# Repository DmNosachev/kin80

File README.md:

# Kin80
Kin80 is a set of replacement PCBs and switch mounting plates for [Kinesis Contoured keyboards](https://deskthority.net/wiki/Kinesis_Contoured).

It is not a drop-in replacement controllers like Stapelberg or KinT (for these controllers I developed a cheap alternative called [kinBP](https://github.com/DmNosachev/kinbp) (will be published soon)). Kin80 uses different matrix (12×7) and it is aimed at serious modding of the Kinesis keyboard.

## Features
- Controller with [QMK firmware](https://qmk.fm/) support.

Uses inexpensive [WeAct Studio STM32F401/STM32F411](https://github.com/WeActTC/MiniSTM32F4x1) MCU board.

The PCB has dimensions less than 100×100 mm. Many manufacturers provide additional discounts for smaller boards.

Additional pads for connecting up to 4 swithes (i.e. additional switches on the keyboard or foot pedals) and 5 free MCU pins.

- Eliminating one of the main drawbacks of Kinesis keyboards (prior to Advantage 2): rubber top row is replaced by with mechanical switches, MX or Kailh Choc.

- Replacement thumb cluster PCBs. Reversible design, additional mounting holes for compatibility with Model 110.

- Thumb cluster switch mounting plates.

## Disadvantages / shortcomings
1. It's obviously more labour intensive than drop-in controller replacement. You have to desolder the key-wells and than carry out hand-wiring of new (or stock) switches. I started designing a PCB for key-wells, but came to the conclusion that flexible boards of this size are too expensive to manufacture.

2. It's necessary to carefully cut out two windows in the keyboard case with Dremel, then glue the mounting plates there. The result will most likely not look very professional. This problem can be solved by 3D printing curved plastic plates, but I don't have the skills to design them.

3. Thumb cluster PCBs require SMD diodes (SOD-323). Soldering them by hand can be tricky for unexperienced people. I'm going to add support for through-hole diodes in the next release.

4. Top row PCB have not been tested yet.

5. Other TODO's: design universal MX/Choc top row PCB, design FR4 mounting plate for the thumb cluster.

## BOM

1. **Controller PCB** (/controller-pcb).
  - [WeAct Studio STM32F401 or STM32F411](https://github.com/WeActTC/MiniSTM32F4x1) board. You can buy them for about 6 USD at the [official Aliexpress store](https://weactstudio.aliexpress.com/). Beware of pirated copies!
  - 2 pcs: 20 cm cable with 11-pin female Micro JST connectors with 1.25 mm pitch ([Aliexpress](https://aliexpress.com/item/4000588750065.html?sku_id=10000003451067244&spm=a2g0o.store_pc_allProduct.8148356.2.6c274451oTiXZp)) for key-wells
  - 2 pcs: 10 cm cable with 7-pin female Micro JST connectors for connecting thumb clusters
  - 2 pcs: cable with 7-pin female Micro JST connectors for connecting top row clusters, 10 cm if using PCBs or 20 cm if using hand-wiring.
  - 2 pcs male Micro JST 11-pin angled or straight connectors
  - 4 pcs male Micro JST 7-pin angled or straight connectors
  - 4 pcs 3-mm LEDs
  - 4 pcs 0805 or through-hole resistors. Their value depends on the type of LEDs (I use 1.5k Ohm for orange LEDs).
  - Pair of USB Type C male and female connectors 
2. **Thumb cluster** (/thumb-pcb)
  - The design is reversible. So, a minimal batch of 5 PCBs will give you 2 pairs + 1 spare.
  - 12 pcs SOD-323 1N4148 diodes.
  - Optional: mounting plates (see /plates/thumb).
  - 2 pcs male Micro JST 7-pin angled connectors
3. **Top row cluster** (/top-pcb)
  - The PCBs are not tested yet. They also have reversible design.
  - 12 pcs SOD-323 1N4148 diodes.
  - PCBs are optional, you can use just plates (/plates/top) and make a hand-wiring with through-hole diodes.
4. **Key-wells**
  - 56 pcs 1N4148 diodes
  - Wire
5. ** Switches **
  - 80 pcs Cherry MX compatible switches or 68 pcs MX + 12 pcs Kailh Choc
  - Optional: switch opener (if you reuse the stock switches)
  
## Buid guide
1. Disassemble the keyboard. Remove all screws and remove all PCBs. Сut the melted pins on the back plates of the top clusters.
2. Desolder the key-well PCBs. If you do not plan to use these PCBs to repair other keyboards, then you can not worry about damaging them.
3. If you plan to reuse the stock switches, then remove the diodes from them (IMHO, it will make further hand-wiring easier). Desolder the switches from thumb cluster PCBs.

You may notice that swiches are glued with hot-melt adhesive. To remove it, just wipe it with isopropyl alcohol. It will not dissolve the glue, but make it lose its adhesive properties.

4. Hand-wire the key-wells. You need *ROW2COL* direction, i.e. the anode of each diode must be connected to a switch pin, cathode (marked by black strip) — to row. See [Modern handwiring guide](https://geekhack.org/index.php?topic=87689.0).

5. Assemble thumb cluster PCBs.
6. Assemble top row PCBs or use hand-wiring.
7. Assemble the controller PCB.

8. Case. Cut two windows for new top row keys. You can use hot-melt adhesive to glue the plates to the case. Seal the holes on the back of the case with pieces of plastic. Glue the USB connector to the back of the case. Optional: use bitumen sound deadening pads to improve acoustics.

9. [Setup the QMK](https://docs.qmk.fm/).
10. Flash the firmware: `qmk flash -kb kin80 -km default`. Hold 'boot0' button on MCU board, press 'reset', then release 'boot0'.

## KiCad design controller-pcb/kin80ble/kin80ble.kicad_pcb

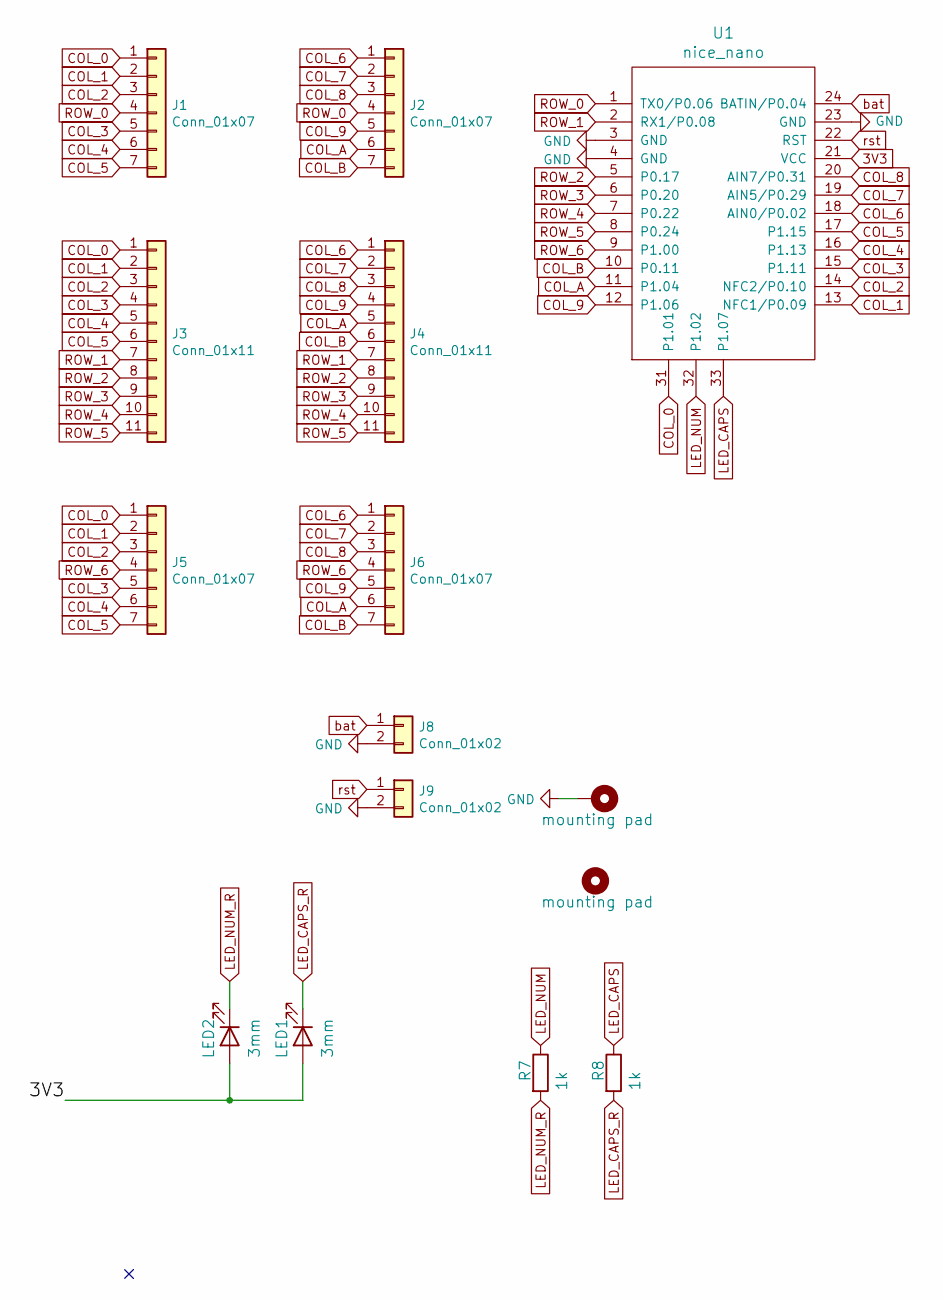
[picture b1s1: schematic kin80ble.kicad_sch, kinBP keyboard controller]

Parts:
H1: mounting pad; MountingHole_4.3mm_M4_Pad
H2: mounting pad; MountingHole_6mm
J1, J2, J5, J6: Conn_01x07; Molex_PicoBlade_53047-0710_1x07_P1.25mm_Vertical
J3, J4: Conn_01x11; Molex_PicoBlade_53047-1110_1x11_P1.25mm_Vertical
J8, J9: Conn_01x02; PinHeader_1x02_P2.54mm_Vertical
LED1, LED2: 3mm; LED_D3.0mm
R7, R8: 1k; R_Axial_DIN0207_L6.3mm_D2.5mm_P7.62mm_Horizontal
U1: nice_nano

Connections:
3V3: LED1.2 (A), LED2.2 (A), U1.21 (VCC)
COL_0: J1.1, J3.1, J5.1, U1.31 (P1.01)
COL_1: J1.2, J3.2, J5.2, U1.13 (NFC1/P0.09)
COL_2: J1.3, J3.3, J5.3, U1.14 (NFC2/P0.10)
COL_3: J1.5, J3.4, J5.5, U1.15 (P1.11)
COL_4: J1.6, J3.5, J5.6, U1.16 (P1.13)
COL_5: J1.7, J3.6, J5.7, U1.17 (P1.15)
COL_6: J2.1, J4.1, J6.1, U1.18 (AIN0/P0.02)
COL_7: J2.2, J4.2, J6.2, U1.19 (AIN5/P0.29)
COL_8: J2.3, J4.3, J6.3, U1.20 (AIN7/P0.31)
COL_9: J2.5, J4.4, J6.5, U1.12 (P1.06)
COL_A: J2.6, J4.5, J6.6, U1.11 (P1.04)
COL_B: J2.7, J4.6, J6.7, U1.10 (P0.11)
GND: H1.1, J8.2, J9.2, U1.3 (GND), U1.4 (GND), U1.23 (GND)
LED_CAPS: R8.1, U1.33 (P1.07); also elsewhere on the board
LED_CAPS_R: LED1.1 (K), R8.2; also elsewhere on the board
LED_NUM: R7.1, U1.32 (P1.02); also elsewhere on the board
LED_NUM_R: LED2.1 (K), R7.2; also elsewhere on the board
ROW_0: J1.4, J2.4, U1.1 (TX0/P0.06)
ROW_1: J3.7, J4.7, U1.2 (RX1/P0.08)
ROW_2: J3.8, J4.8, U1.5 (P0.17)
ROW_3: J3.9, J4.9, U1.6 (P0.20)
ROW_4: J3.10, J4.10, U1.7 (P0.22)
ROW_5: J3.11, J4.11, U1.8 (P0.24)
ROW_6: J5.4, J6.4, U1.9 (P1.00)
bat: J8.1, U1.24 (BATIN/P0.04)
rst: J9.1, U1.22 (RST)

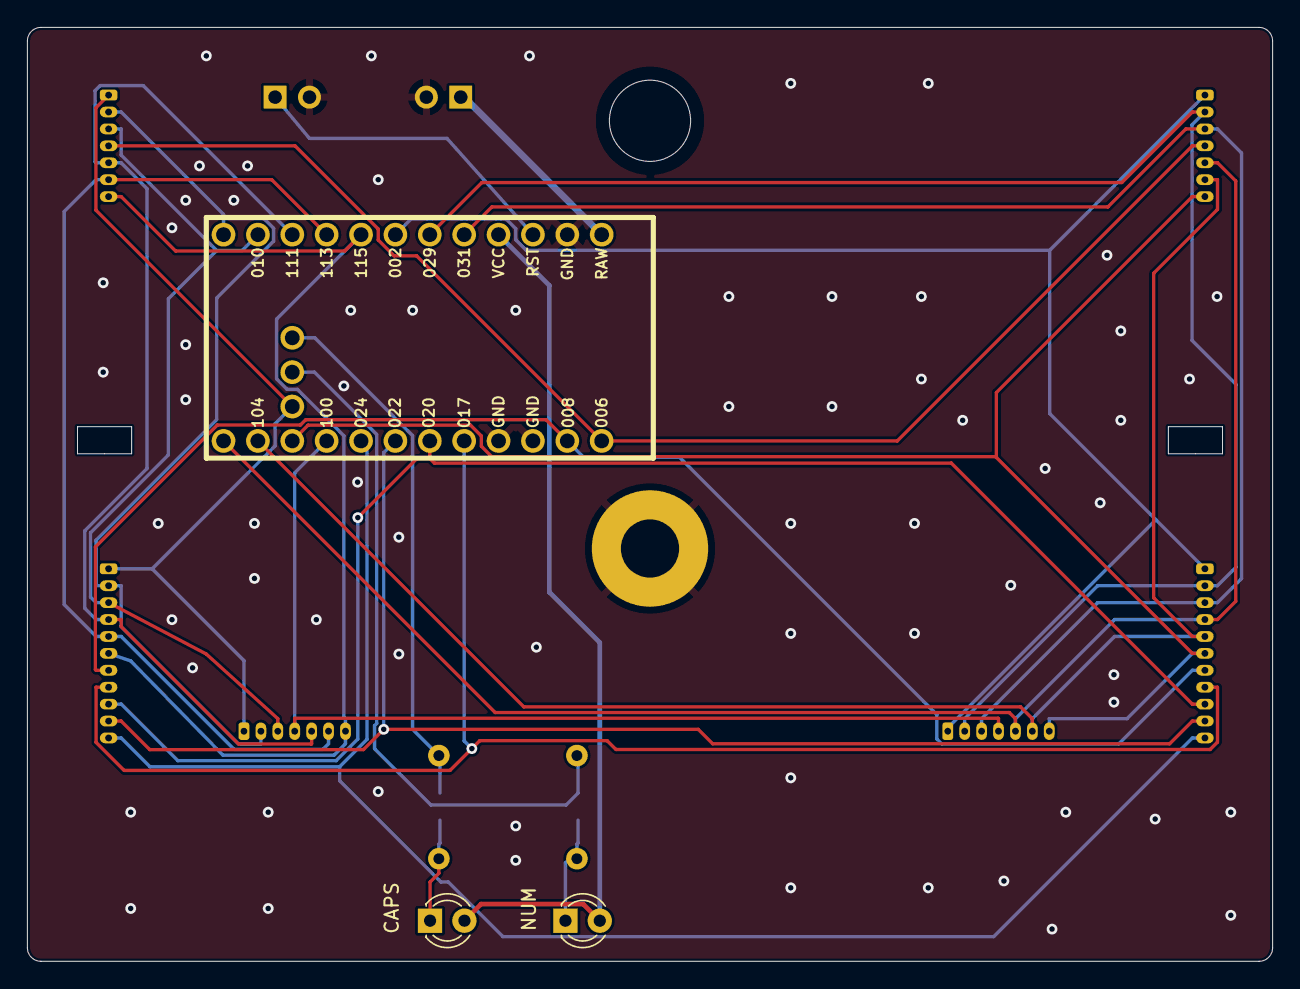
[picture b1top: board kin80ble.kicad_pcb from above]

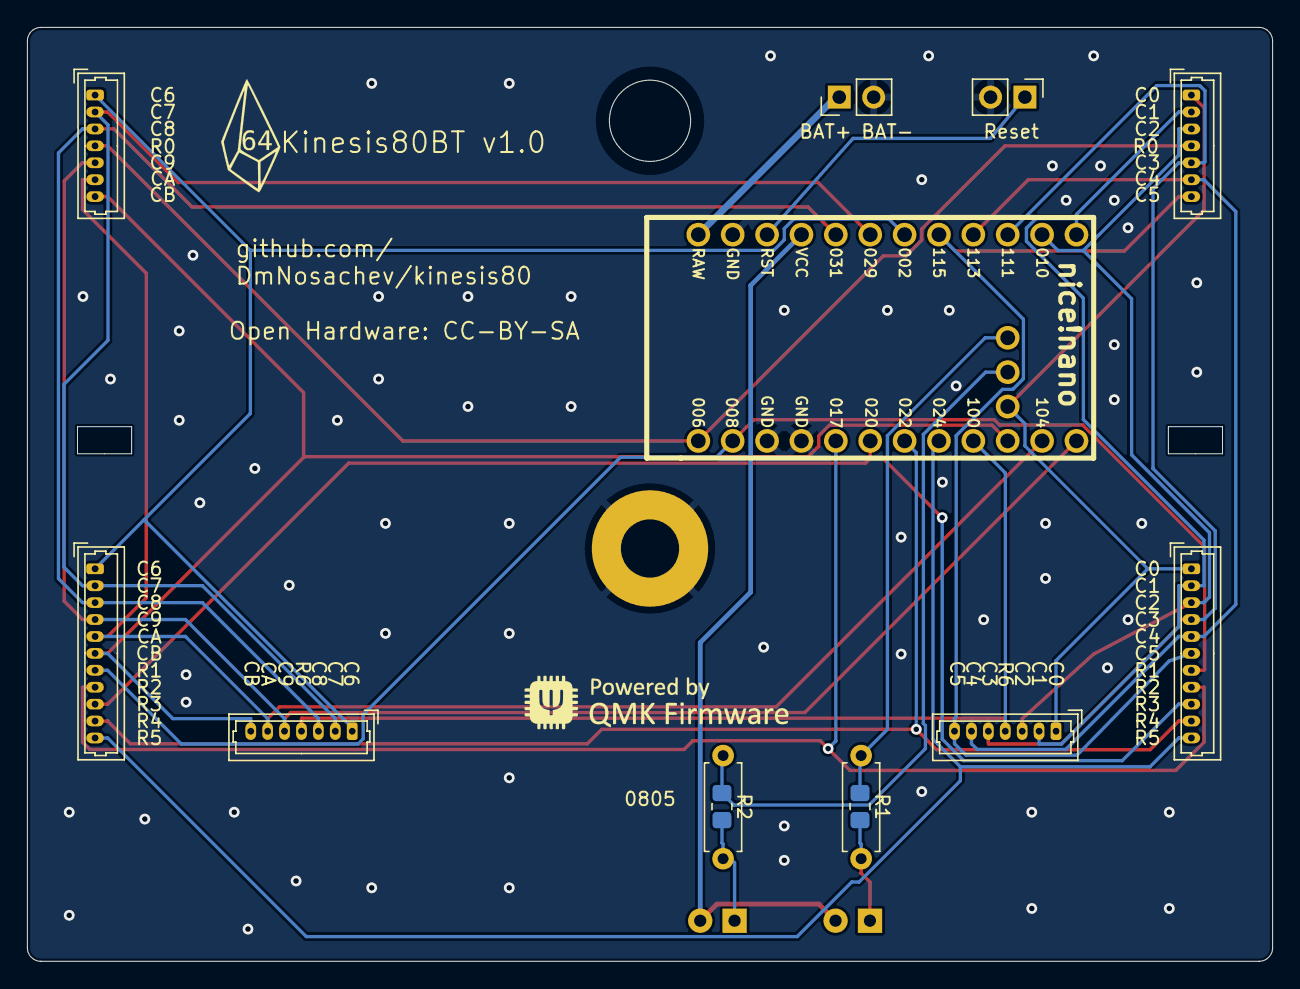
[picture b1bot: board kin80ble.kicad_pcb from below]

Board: 2 copper layers, 92.0 x 69.0 mm, 19 parts (15 on the bottom side), 27 nets.

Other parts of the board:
G1: LOGO; q64logo
G2: LOGO; qmk-small
R1, R2: 1k; R_0805_2012Metric_Pad1.20x1.40mm_HandSolder

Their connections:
LED_CAPS: R1.1; also elsewhere on the board
LED_CAPS_R: R1.2; also elsewhere on the board
LED_NUM: R2.1; also elsewhere on the board
LED_NUM_R: R2.2; also elsewhere on the board

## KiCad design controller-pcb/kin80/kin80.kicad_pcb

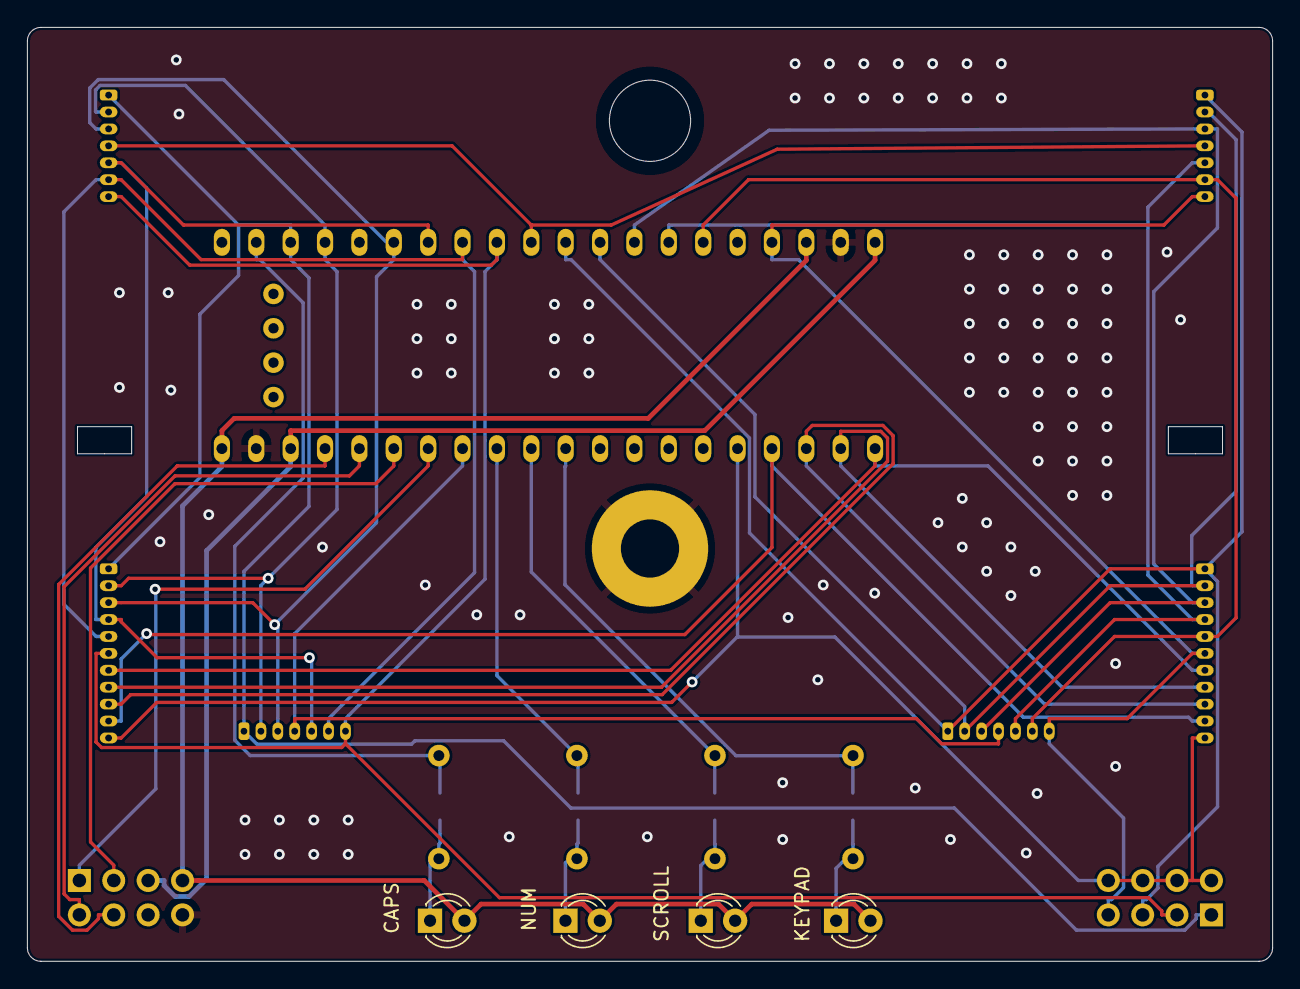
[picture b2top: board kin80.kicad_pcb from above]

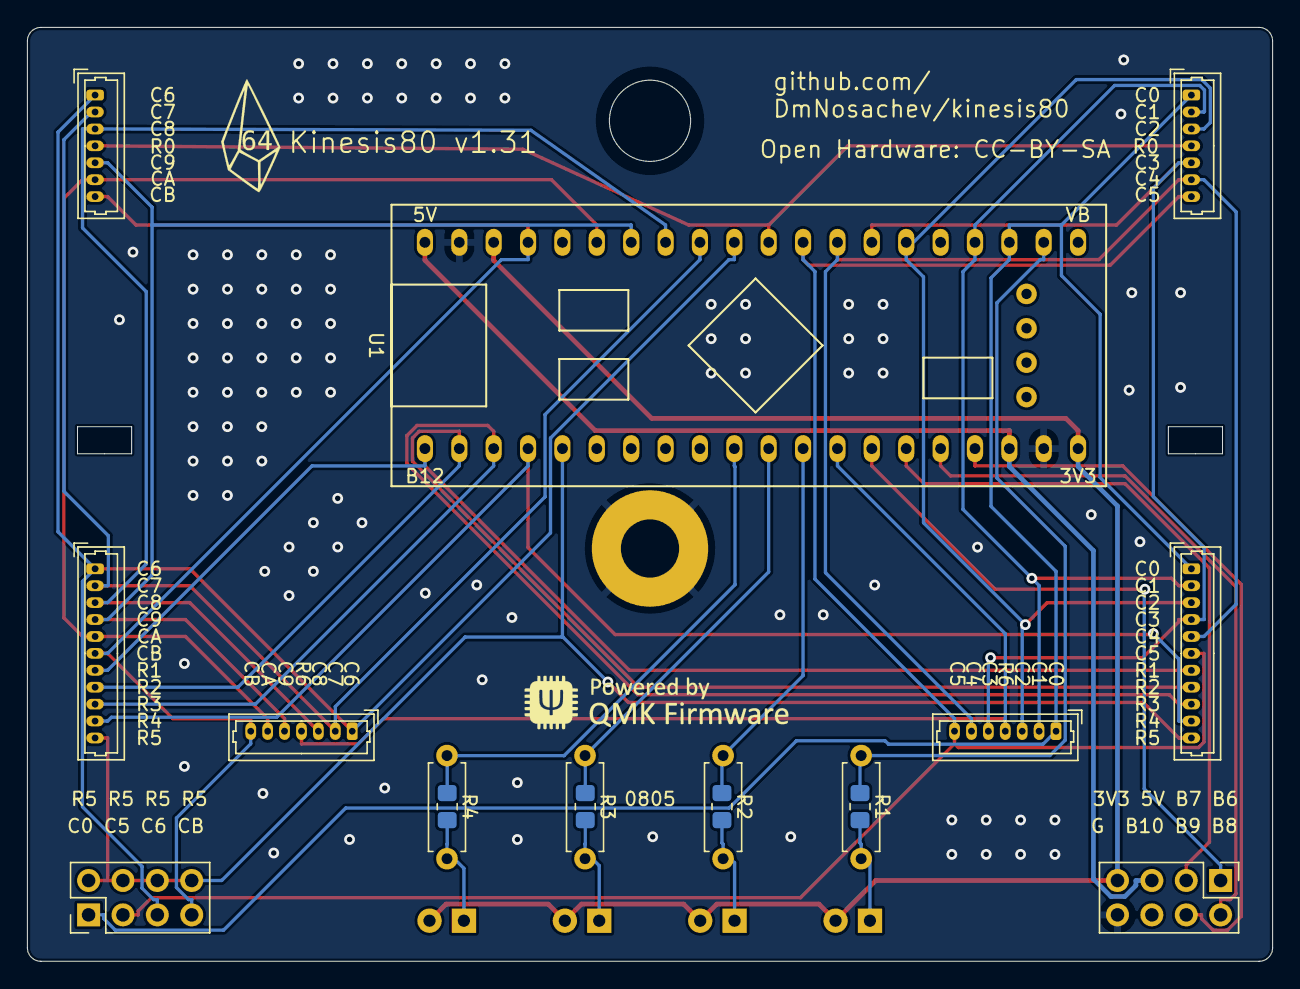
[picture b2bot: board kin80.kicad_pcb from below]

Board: 2 copper layers, 92.0 x 69.0 mm, 25 parts (19 on the bottom side), 34 nets.

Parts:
G1: LOGO; q64logo
G2: LOGO; qmk-small
H1: mounting pad; MountingHole_4.3mm_M4_Pad
H2: mounting pad; MountingHole_6mm
J1, J2, J5, J6: Conn_01x07; Molex_PicoBlade_53047-0710_1x07_P1.25mm_Vertical
J3, J4: Conn_01x11; Molex_PicoBlade_53047-1110_1x11_P1.25mm_Vertical
J7, J8: Conn_02x04_Odd_Even; PinHeader_2x04_P2.54mm_Vertical
LED1, LED2, LED3, LED4: 3mm; LED_D3.0mm
R1, R2, R3, R4: 1k; R_0805_2012Metric_Pad1.20x1.40mm_HandSolder
R5, R6, R7, R8: 1k; R_Axial_DIN0207_L6.3mm_D2.5mm_P7.62mm_Horizontal
U1: weact_STM32F4x1; STM32F4x1_MiniF4

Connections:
3V3: J8.7, LED1.2, LED2.2, LED3.2, LED4.2, U1.20, U1.38
5V: J8.5, U1.18, U1.40
B8: J8.2, U1.16
B9: J8.4, U1.17
COL_0: J1.1, J3.1, J5.1, J7.1, U1.23
COL_1: J1.2, J3.2, J5.2, U1.24
COL_2: J1.3, J3.3, J5.3, U1.26
COL_3: J1.5, J3.4, J5.5, U1.27
COL_4: J1.6, J3.5, J5.6, U1.28
COL_5: J1.7, J3.6, J5.7, J7.3, U1.29
COL_6: J2.1, J4.1, J6.1, J7.5, U1.31
COL_7: J2.2, J4.2, J6.2, U1.32
COL_8: J2.3, J4.3, J6.3, U1.33
COL_9: J2.5, J4.4, J6.5, U1.34
COL_A: J2.6, J4.5, J6.6, U1.35
COL_B: J2.7, J4.6, J6.7, J7.7, U1.37
GND: H1.1, J8.8, U1.19, U1.39
LED_CAPS: R1.1, R8.1, U1.22
LED_CAPS_R: LED1.1, R1.2, R8.2
LED_KPD: R4.1, R5.1, U1.10
LED_KPD_R: LED4.1, R4.2, R5.2
LED_NUM: R2.1, R7.1, U1.12
LED_NUM_R: LED2.1, R2.2, R7.2
LED_SCRL: R3.1, R6.1, U1.11
LED_SCRL_R: LED3.1, R3.2, R6.2
ROW_0: J1.4, J2.4, U1.30
ROW_1: J3.7, J4.7, U1.1
ROW_2: J3.8, J4.8, U1.2
ROW_3: J3.9, J4.9, U1.3
ROW_4: J3.10, J4.10, U1.4
ROW_5: J3.11, J4.11, J7.2, J7.4, J7.6, J7.8, U1.5
ROW_6: J5.4, J6.4, U1.13
SCL1: J8.1, U1.14
SDA1: J8.3, U1.15

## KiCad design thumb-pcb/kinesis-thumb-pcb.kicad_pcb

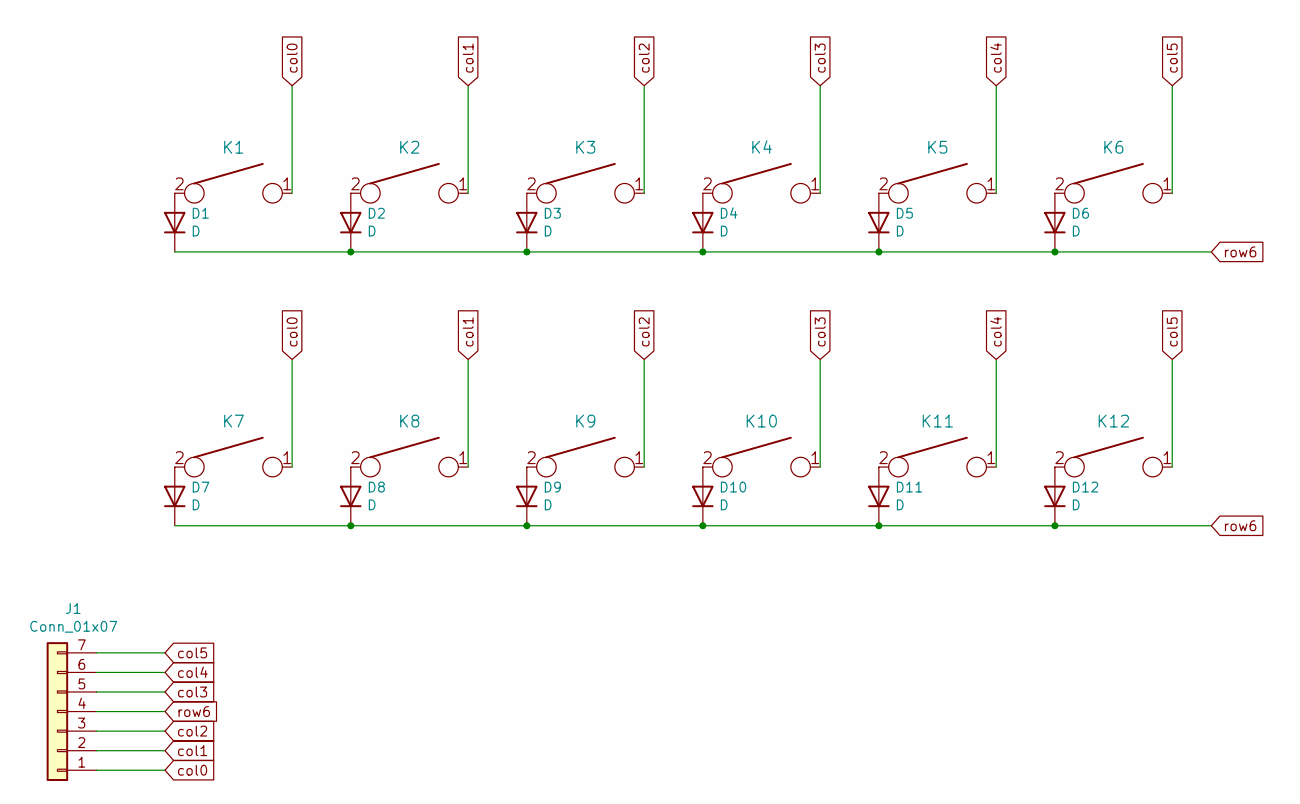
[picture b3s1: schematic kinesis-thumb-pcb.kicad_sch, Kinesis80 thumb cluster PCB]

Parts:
D1, D2, D3, D4, D5, D6, D7, D8, D9, D10, D11, D12: D; D_SOD-323_HandSoldering
J1: Conn_01x07; Molex_PicoBlade_53047-0710_1x07_P1.25mm_Vertical
K1, K2, K3, K4, K5, K6: KEYSW; MXOnly-1U-NoLED
K7, K8, K9, K10, K11, K12: KEYSW; MXOnly-1U-NoLED-twin

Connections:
unnamed: D1.2 (A), K1.2
unnamed: D2.2 (A), K2.2
unnamed: D3.2 (A), K3.2
unnamed: D4.2 (A), K4.2
unnamed: D5.2 (A), K5.2
unnamed: D6.2 (A), K6.2
unnamed: D7.2 (A), K7.2
unnamed: D8.2 (A), K8.2
unnamed: D9.2 (A), K9.2
unnamed: D10.2 (A), K10.2
unnamed: D11.2 (A), K11.2
unnamed: D12.2 (A), K12.2
col0: J1.1, K1.1, K7.1
col1: J1.2, K2.1, K8.1
col2: J1.3, K3.1, K9.1
col3: J1.5, K4.1, K10.1
col4: J1.6, K5.1, K11.1
col5: J1.7, K6.1, K12.1
row6: D1.1 (K), D2.1 (K), D3.1 (K), D4.1 (K), D5.1 (K), D6.1 (K), D7.1 (K), D8.1 (K), D9.1 (K), D10.1 (K), D11.1 (K), D12.1 (K), J1.4

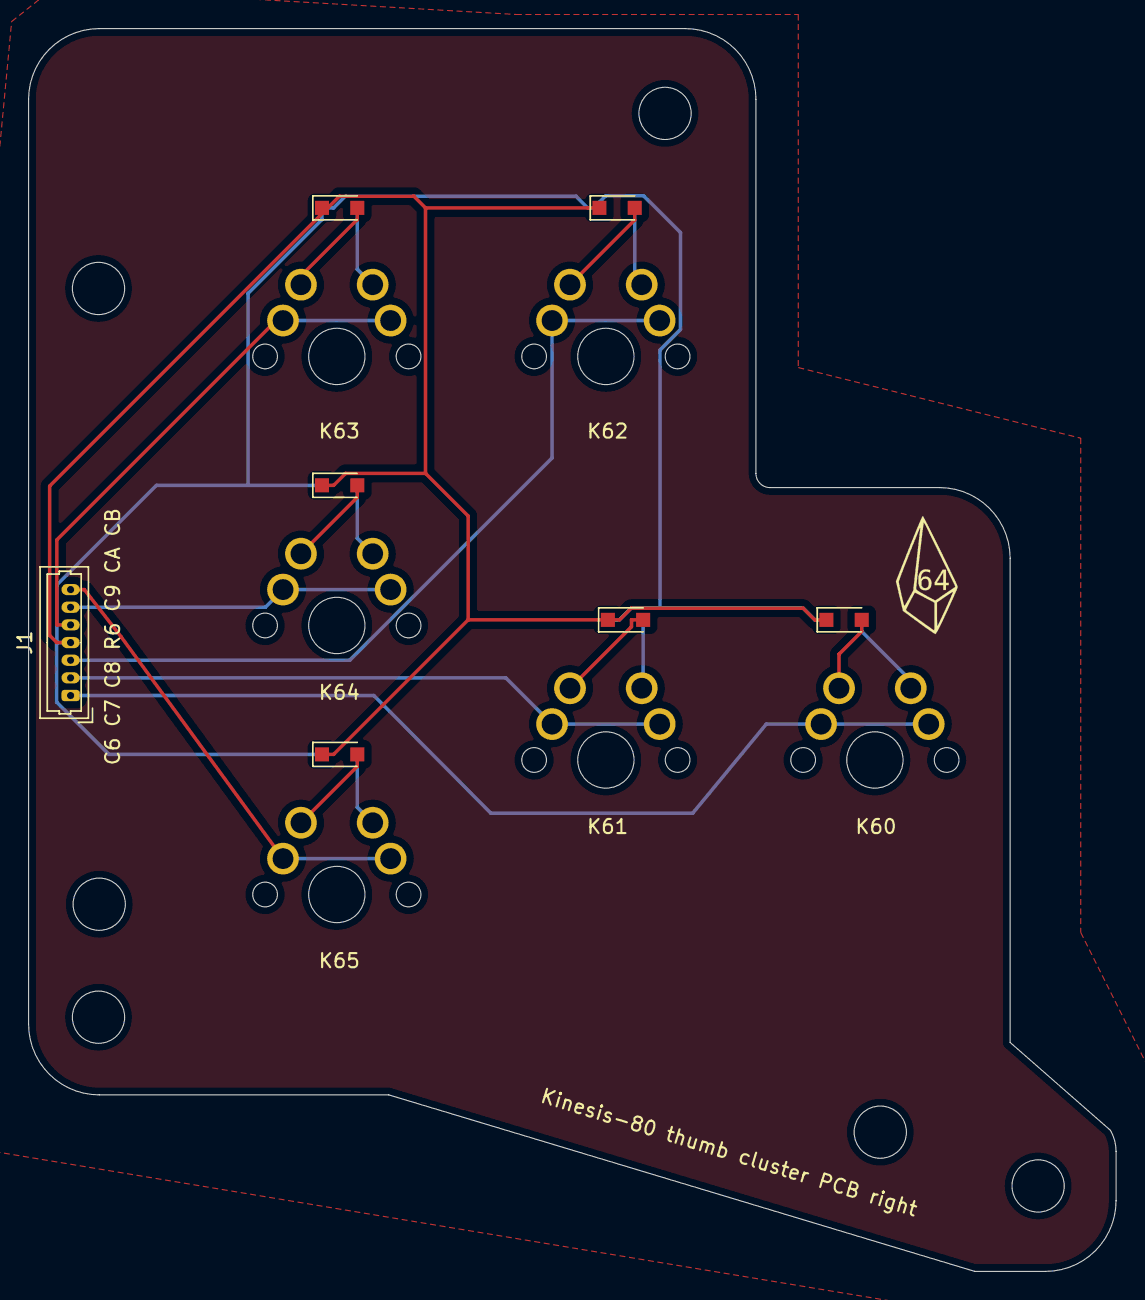
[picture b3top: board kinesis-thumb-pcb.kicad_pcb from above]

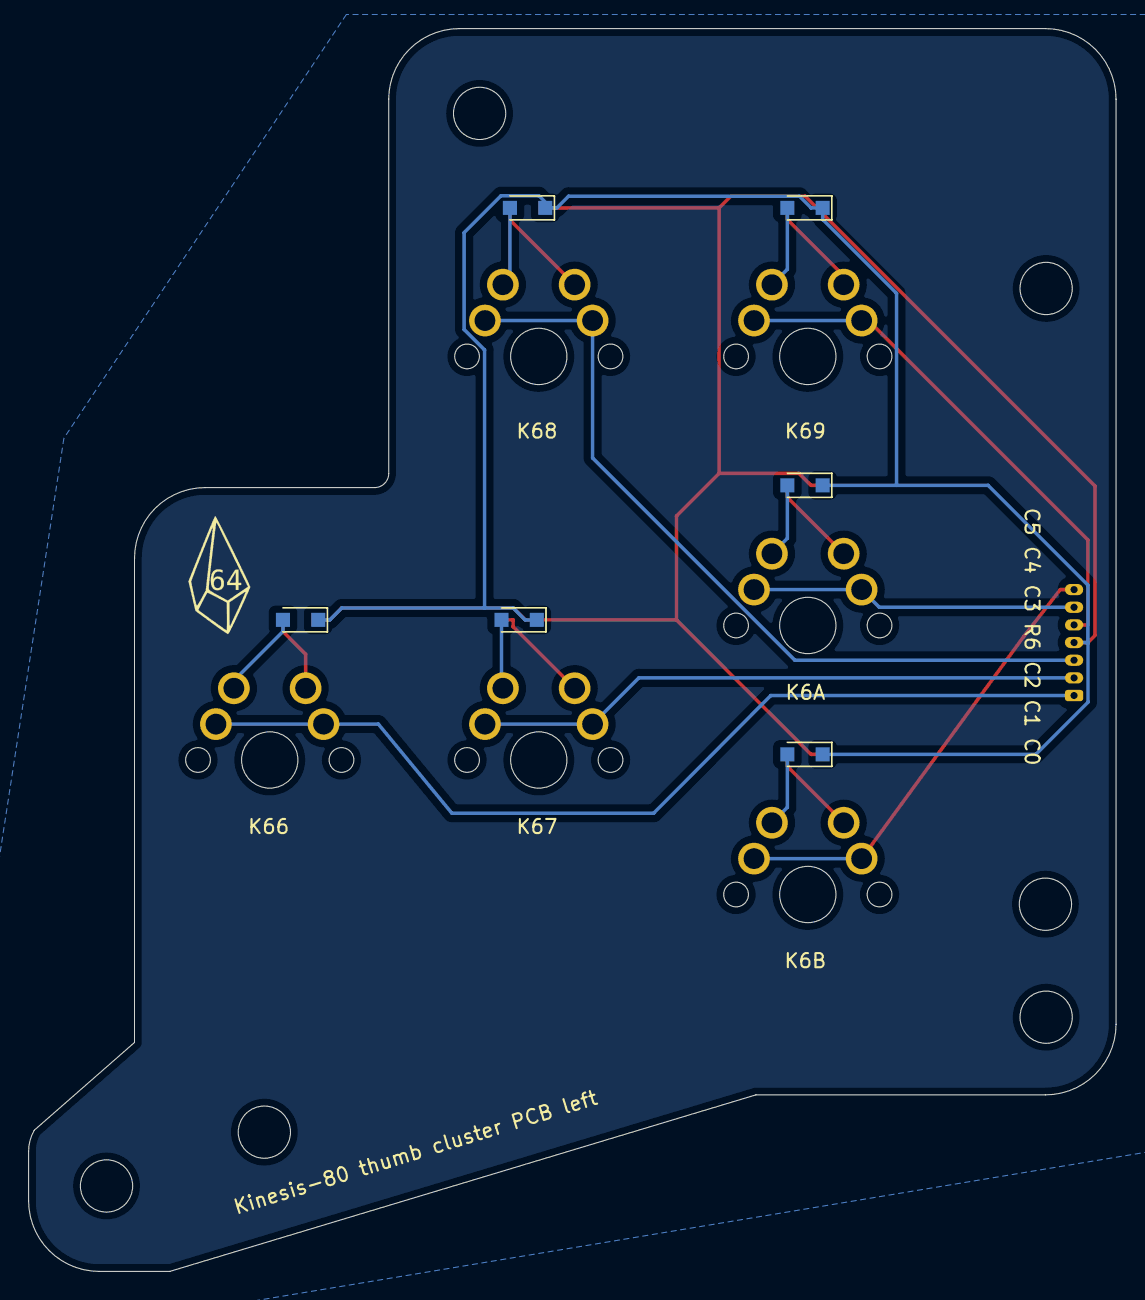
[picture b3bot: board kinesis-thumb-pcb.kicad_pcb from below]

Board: 2 copper layers, 77.0 x 88.0 mm, 33 parts (19 on the bottom side), 19 nets.

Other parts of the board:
G1, G2: LOGO; q64logo
REF1, REF2, REF3, REF4, REF5, REF6: MountingHole_3.7mm

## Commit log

2022-03-15 1.31 release
2022-03-15 other PCBs and plates
2022-03-17 Updated documentation
2022-03-18 Update README.md
    Renamed to Kin80
2022-04-19 PCB files

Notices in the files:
controller-pcb/kin80/kin80.kicad_pcb:
Open Hardware: CC-BY-SA
